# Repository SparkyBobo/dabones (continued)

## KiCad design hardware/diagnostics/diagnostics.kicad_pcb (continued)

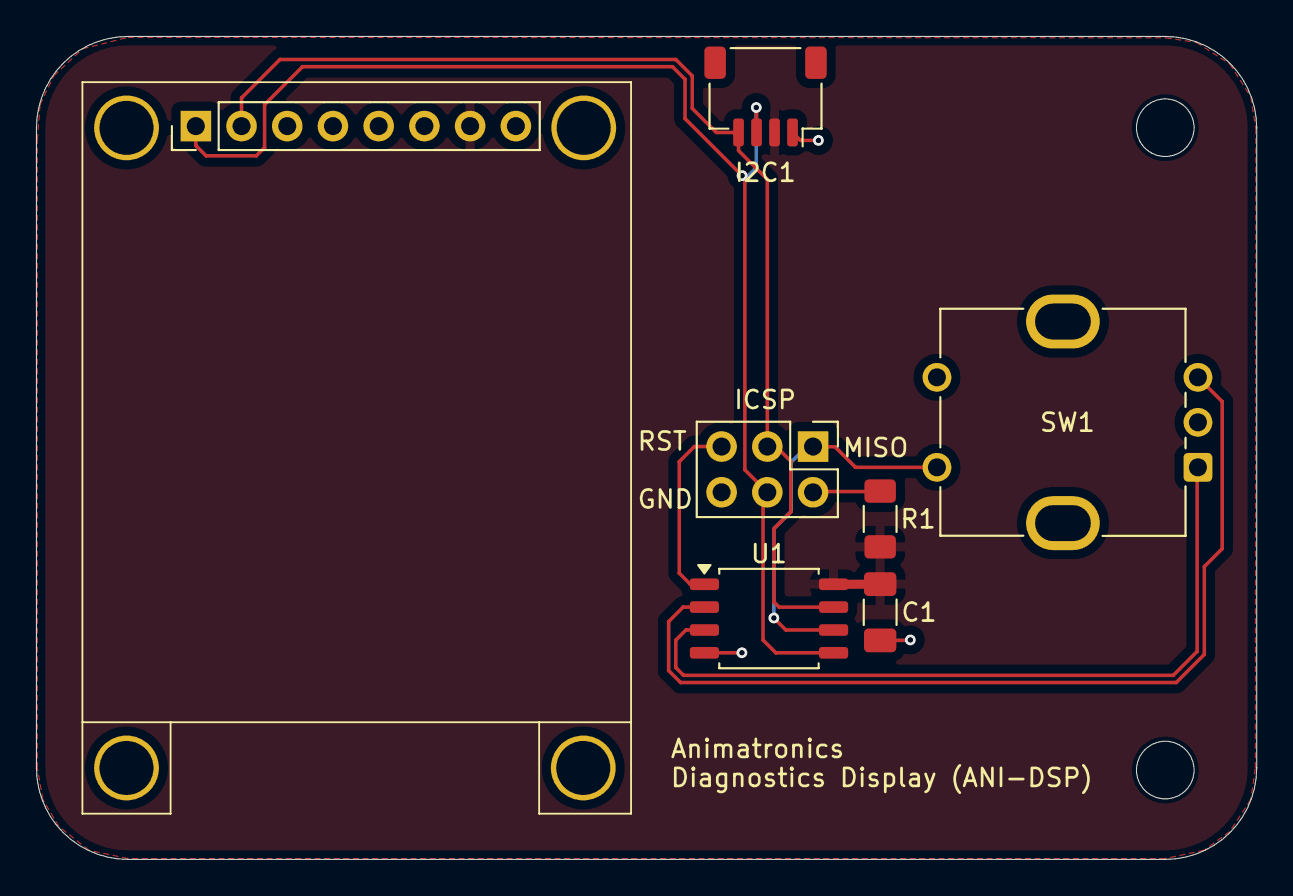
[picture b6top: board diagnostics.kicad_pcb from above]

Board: 2 copper layers, 67.8 x 45.7 mm, 9 parts (0 on the bottom side), 9 nets.

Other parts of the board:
R1: 330; R_1206_3216Metric_Pad1.30x1.75mm_HandSolder

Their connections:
+3.3V: R1.1; also elsewhere on the board
unnamed 8: R1.2; also elsewhere on the board

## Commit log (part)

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2024-12-30 Initial commit.
2025-02-15 Hardware Rev 1.0
2026-01-01 Rev 1.1: - Update to latest KiCad - Fixed short in servo board - Updates to right-angle diag connector on servo boards - Fixed microproc footprint on diag board - Flipped I2C connector to top of diag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
2026-01-02 Initial commit of midi docs.
2026-01-02 Remove whitespace.
2026-01-03 Update the midi docs to enable development of midi parsing and sequencer.
